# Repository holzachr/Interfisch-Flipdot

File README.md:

This is a fork of "Interfisch"'s brilliant work for creating an ESP32 based "Annax" flipdot module controller board, software and more.

The goals of this fork are
- Re-layouting the controller board to fit the original ADtranz controller board
- Modifying the ESP32 software to support the original ADtranz flipdot module configuration (2x 25x16, 2x 20x16, 1x 25x16)
- Added another useful test pattern (checkers)
- Made flipdot timing parameters settable through MQTT, to help determine ideal settings

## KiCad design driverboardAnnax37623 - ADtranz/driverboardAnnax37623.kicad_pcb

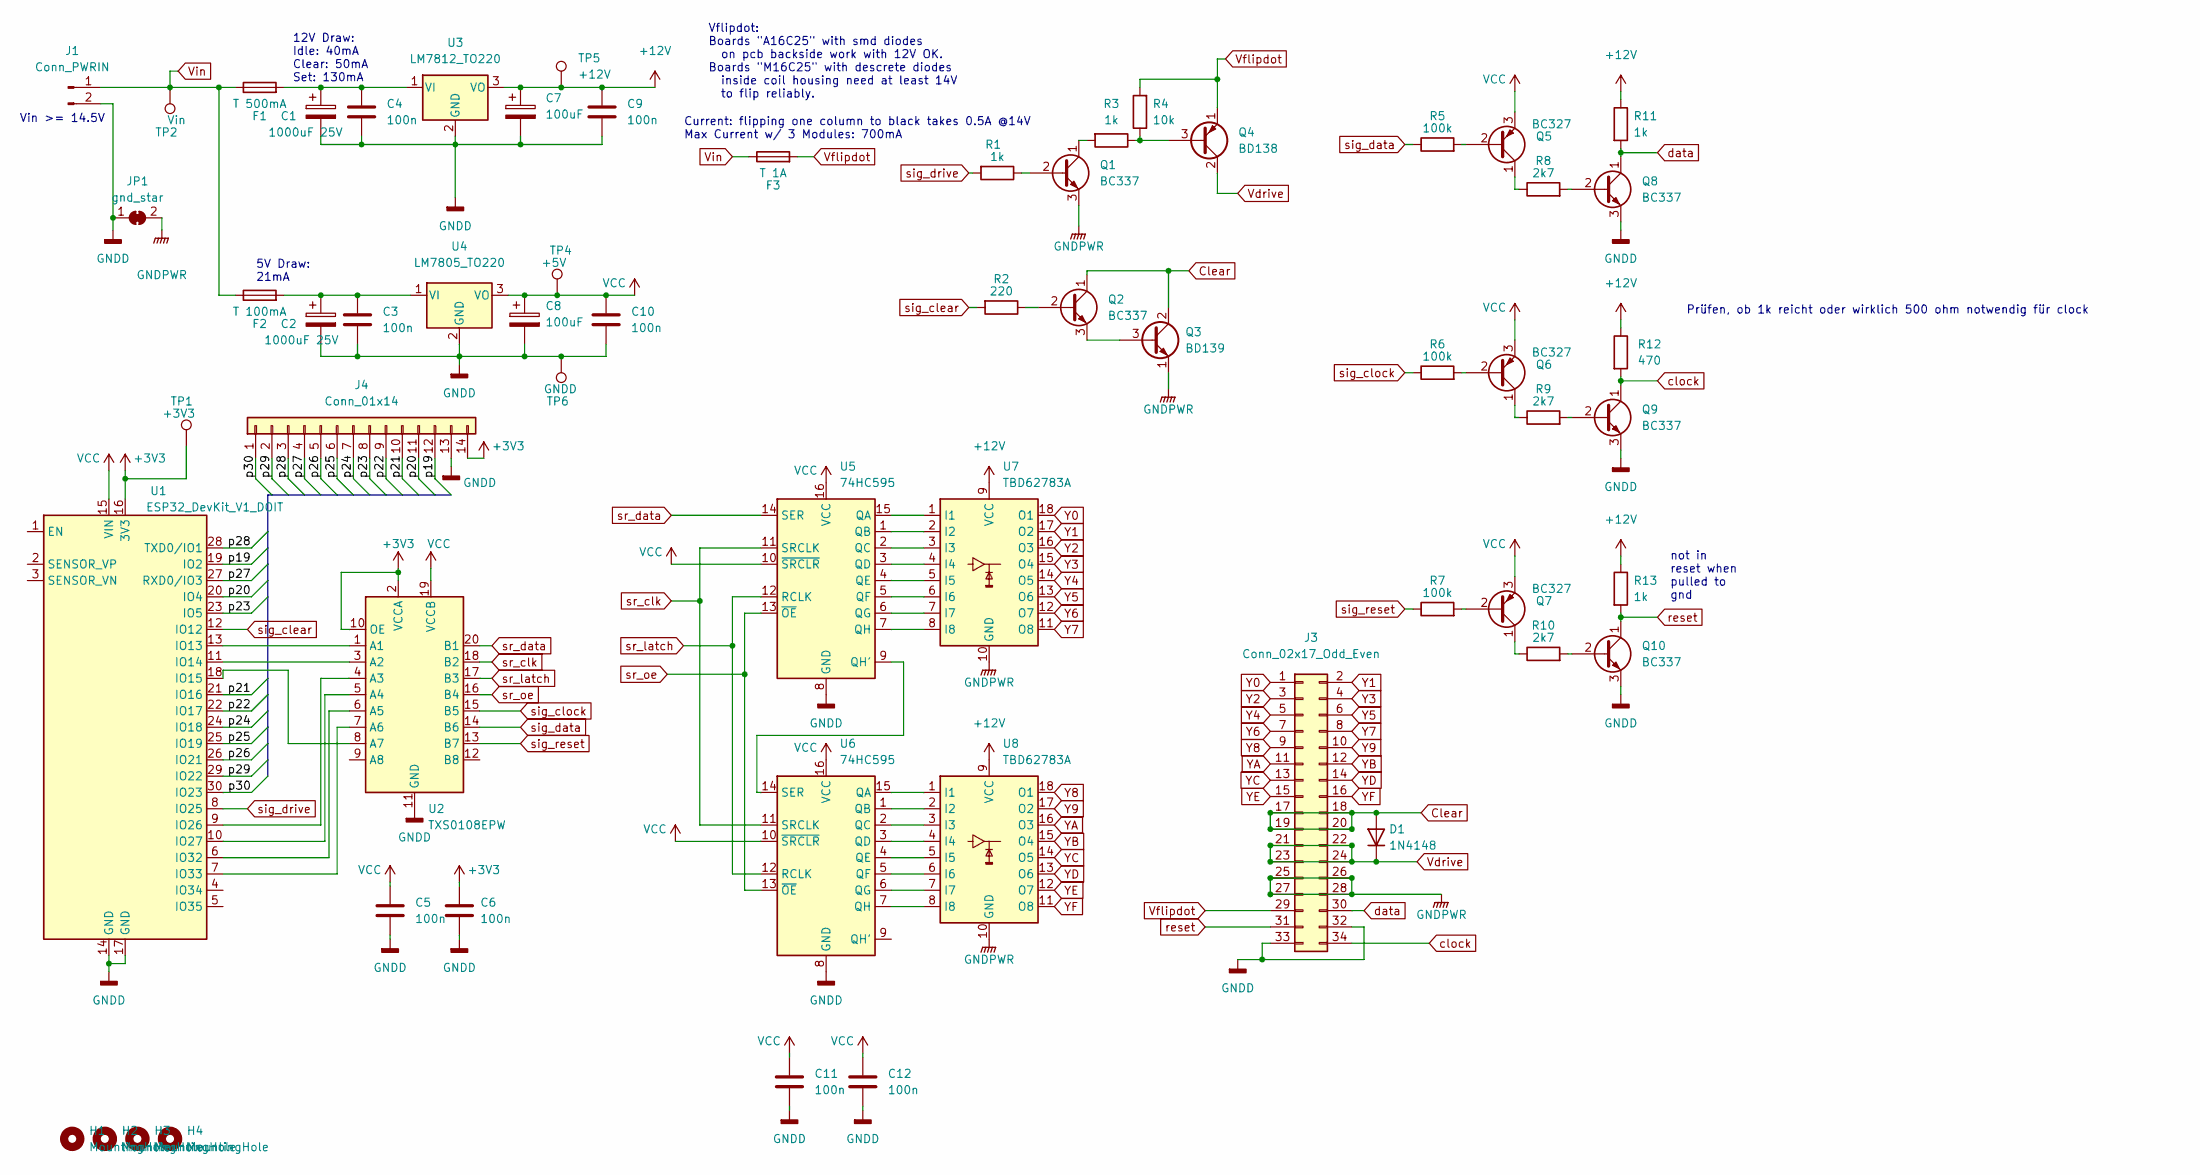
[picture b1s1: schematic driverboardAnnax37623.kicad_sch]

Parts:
C1, C2: 1000uF 25V; CP_Radial_D10.0mm_P5.00mm
C3, C4, C5, C6, C9, C10, C11, C12: 100n; C_Disc_D3.0mm_W2.0mm_P2.50mm
C7, C8: 100uF; CP_Radial_D10.0mm_P5.00mm
D1: 1N4148; D_DO-35_SOD27_P7.62mm_Horizontal
F1: T 500mA; Fuseholder_Clip-5x20mm_Littelfuse_100_Inline_P20.50x4.60mm_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
F2: T 100mA; Fuseholder_Clip-5x20mm_Littelfuse_100_Inline_P20.50x4.60mm_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
F3: T 1A; Fuseholder_Clip-5x20mm_Littelfuse_100_Inline_P20.50x4.60mm_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
H1, H3: MountingHole; MountingHole_4mm
H2, H4: MountingHole; MountingHole_5mm
J1: Conn_PWRIN; TerminalBlock_bornier-2_P5.08mm
J3: Conn_02x17_Odd_Even; IDC-Header_2x17_P2.54mm_Vertical
J4: Conn_01x14; PinHeader_1x14_P2.54mm_Vertical
JP1: gnd_star; PinHeader_1x02_P2.54mm_Vertical
Q1, Q2, Q8, Q9, Q10: BC337; TO-92_Inline
Q3: BD139; TO-126-3_Vertical
Q4: BD138; TO-126-3_Vertical
Q5, Q6, Q7: BC327; TO-92_Inline
R1, R3, R11, R13: 1k; R_Axial_DIN0207_L6.3mm_D2.5mm_P10.16mm_Horizontal
R2: 220; R_Axial_DIN0207_L6.3mm_D2.5mm_P10.16mm_Horizontal
R4: 10k; R_Axial_DIN0207_L6.3mm_D2.5mm_P10.16mm_Horizontal
R5, R6, R7: 100k; R_Axial_DIN0207_L6.3mm_D2.5mm_P10.16mm_Horizontal
R8, R9, R10: 2k7; R_Axial_DIN0207_L6.3mm_D2.5mm_P10.16mm_Horizontal
R12: 470; R_Axial_DIN0207_L6.3mm_D2.5mm_P10.16mm_Horizontal
TP1: +3V3; TestPoint_Bridge_Pitch2.54mm_Drill1.0mm
TP2: Vin; TestPoint_Bridge_Pitch2.54mm_Drill1.0mm
TP4: +5V; TestPoint_Bridge_Pitch2.54mm_Drill1.0mm
TP5: +12V; TestPoint_Bridge_Pitch2.54mm_Drill1.0mm
TP6: GNDD; TestPoint_Bridge_Pitch2.54mm_Drill1.0mm
U1: ESP32_DevKit_V1_DOIT; esp32_devkit_v1_doit
U2: TXS0108EPW; TSSOP-20_4.4x6.5mm_P0.65mm
U3: LM7812_TO220; TO-220-3_Vertical
U4: LM7805_TO220; TO-220-3_Vertical
U5, U6: 74HC595; DIP-16_W7.62mm_Socket_LongPads
U7, U8: TBD62783A; DIP-18_W7.62mm_LongPads

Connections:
+3V3: C6.1, J4.14, TP1.1, U1.16 (3V3), U2.2 (VCCA), U2.10 (OE)
+12V: C7.1, C9.1, R11.1, R12.1, R13.1, TP5.1, U3.3 (VO), U7.9 (VCC), U8.9 (VCC)
/p19: J4.12, U1.19 (IO2)
/p20: J4.11, U1.20 (IO4)
/p21: J4.10, U1.21 (IO16)
/p22: J4.9, U1.22 (IO17)
/p23: J4.8, U1.23 (IO5)
/p24: J4.7, U1.24 (IO18)
/p25: J4.6, U1.25 (IO19)
/p26: J4.5, U1.26 (IO21)
/p27: J4.4, U1.27 (RXD0/IO3)
/p28: J4.3, U1.28 (TXD0/IO1)
/p29: J4.2, U1.29 (IO22)
/p30: J4.1, U1.30 (IO23)
Clear: D1.2 (A), J3.17, J3.18, J3.19, J3.20, Q2.1 (C), Q3.2 (C)
GNDD: C1.2, C2.2, C3.2, C4.2, C5.2, C6.2, C7.2, C8.2, C9.2, C10.2, C11.2, C12.2, J1.2, J3.32, J3.33, J4.13, JP1.1 (A), Q8.3 (E), Q9.3 (E), Q10.3 (E), TP6.1, U1.14 (GND), U1.17 (GND), U2.11 (GND), U3.2 (GND), U4.2 (GND), U5.8 (GND), U6.8 (GND)
GNDPWR: J3.25, J3.26, J3.27, J3.28, JP1.2 (B), Q1.3 (E), Q3.1 (E), U7.10 (GND), U8.10 (GND)
unnamed: Q1.2 (B), R1.1
unnamed: Q1.1 (C), R3.2
unnamed: Q2.2 (B), R2.1
unnamed: Q2.3 (E), Q3.3 (B)
unnamed: Q4.3 (B), R3.1, R4.1
unnamed: Q5.2 (B), R5.2
unnamed: Q5.1 (C), R8.1
unnamed: Q6.2 (B), R6.2
unnamed: Q6.1 (C), R9.1
unnamed: Q7.2 (B), R7.2
unnamed: Q7.1 (C), R10.1
unnamed: Q8.2 (B), R8.2
unnamed: Q9.2 (B), R9.2
unnamed: Q10.2 (B), R10.2
unnamed: U1.13 (IO13), U2.1 (A1)
unnamed: U1.11 (IO14), U2.3 (A2)
unnamed: U1.18 (IO15), U2.8 (A7)
unnamed: U1.9 (IO26), U2.4 (A3)
unnamed: U1.10 (IO27), U2.5 (A4)
unnamed: U1.6 (IO32), U2.6 (A5)
unnamed: U1.7 (IO33), U2.7 (A6)
unnamed: C1.1, C4.1, F1.2, U3.1 (VI)
unnamed: C2.1, C3.1, F2.2, U4.1 (VI)
unnamed: U5.15 (QA), U7.1 (I1)
unnamed: U5.1 (QB), U7.2 (I2)
unnamed: U5.2 (QC), U7.3 (I3)
unnamed: U5.3 (QD), U7.4 (I4)
unnamed: U5.4 (QE), U7.5 (I5)
unnamed: U5.5 (QF), U7.6 (I6)
unnamed: U5.6 (QG), U7.7 (I7)
unnamed: U5.9 (QH'), U6.14 (SER)
unnamed: U5.7 (QH), U7.8 (I8)
unnamed: U6.15 (QA), U8.1 (I1)
unnamed: U6.1 (QB), U8.2 (I2)
unnamed: U6.2 (QC), U8.3 (I3)
unnamed: U6.3 (QD), U8.4 (I4)
unnamed: U6.4 (QE), U8.5 (I5)
unnamed: U6.5 (QF), U8.6 (I6)
unnamed: U6.6 (QG), U8.7 (I7)
unnamed: U6.7 (QH), U8.8 (I8)
VCC: C5.1, C8.1, C10.1, C11.1, C12.1, Q5.3 (E), Q6.3 (E), Q7.3 (E), TP4.1, U1.15 (VIN), U2.19 (VCCB), U4.3 (VO), U5.10 (~SRCLR), U5.16 (VCC), U6.10 (~SRCLR), U6.16 (VCC)
Vdrive: D1.1 (K), J3.21, J3.22, J3.23, J3.24, Q4.2 (C)
Vflipdot: F3.2, J3.29, Q4.1 (E), R4.2
Vin: F1.1, F2.1, F3.1, J1.1, TP2.1
Y0: J3.1, U7.18 (O1)
Y1: J3.2, U7.17 (O2)
Y2: J3.3, U7.16 (O3)
Y3: J3.4, U7.15 (O4)
Y4: J3.5, U7.14 (O5)
Y5: J3.6, U7.13 (O6)
Y6: J3.7, U7.12 (O7)
Y7: J3.8, U7.11 (O8)
Y8: J3.9, U8.18 (O1)
Y9: J3.10, U8.17 (O2)
YA: J3.11, U8.16 (O3)
YB: J3.12, U8.15 (O4)
YC: J3.13, U8.14 (O5)
YD: J3.14, U8.13 (O6)
YE: J3.15, U8.12 (O7)
YF: J3.16, U8.11 (O8)
clock: J3.34, Q9.1 (C), R12.2
data: J3.30, Q8.1 (C), R11.2
reset: J3.31, Q10.1 (C), R13.2
sig_clear: R2.2, U1.12 (IO12)
sig_clock: R6.1, U2.15 (B5)
sig_data: R5.1, U2.14 (B6)
sig_drive: R1.2, U1.8 (IO25)
sig_reset: R7.1, U2.13 (B7)
sr_clk: U2.18 (B2), U5.11 (SRCLK), U6.11 (SRCLK)
sr_data: U2.20 (B1), U5.14 (SER)
sr_latch: U2.17 (B3), U5.12 (RCLK), U6.12 (RCLK)
sr_oe: U2.16 (B4), U5.13 (~OE), U6.13 (~OE)

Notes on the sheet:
Vin >= 14.5V
5V Draw: 21mA
not in reset when pulled to gnd
Current: flipping one column to black takes 0.5A @14V Max Current w/ 3 Modules: 700mA
Prüfen, ob 1k reicht oder wirklich 500 ohm notwendig für clock
Vflipdot: Boards "A16C25" with smd diodes on pcb backside work with 12V OK. Boards "M16C25" with descrete diodes inside coil housing need at least 14V to flip reliably.
12V Draw: Idle: 40mA Clear: 50mA Set: 130mA

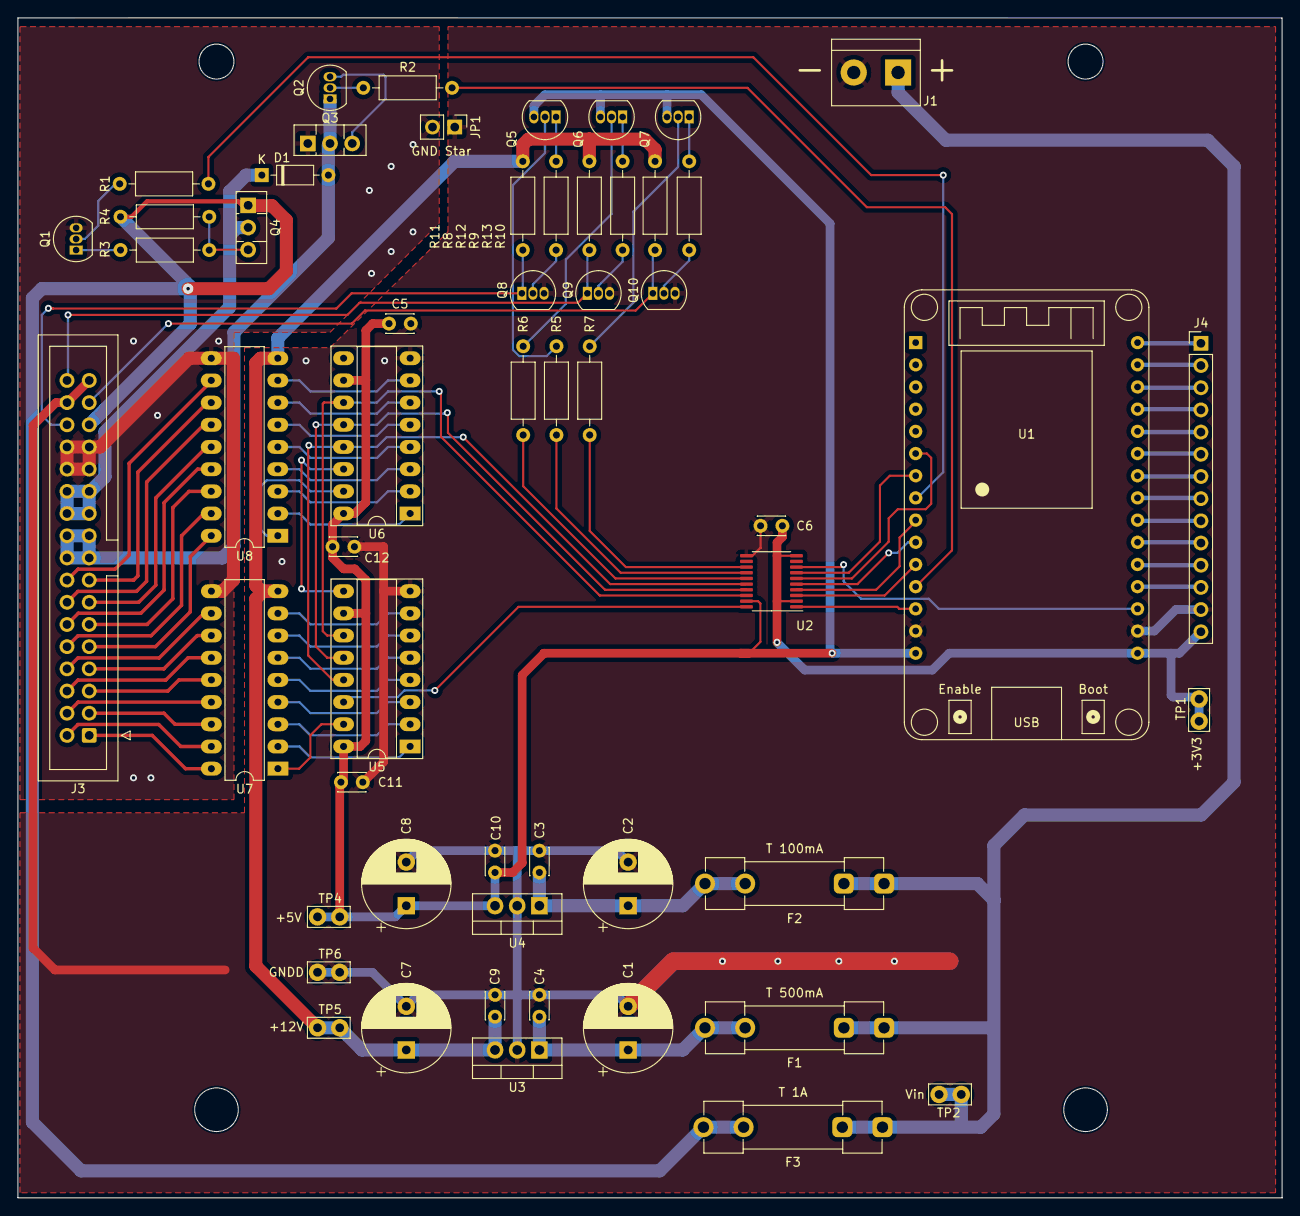
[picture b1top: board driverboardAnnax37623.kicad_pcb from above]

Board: 2 copper layers, 144.7 x 135.1 mm, 60 parts (0 on the bottom side), 89 nets.

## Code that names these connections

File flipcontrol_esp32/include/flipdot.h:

#ifndef FLIPDOT_H
#define FLIPDOT_H

#include <Arduino.h>

#define CHECK_BIT(var,pos) ((var) & (1<<(pos)))

/*
D7 - Ser (data)
D5 - clock
D1 - _OE
D2 - latch
D3 - _clear
*/

//Pins connected to Shift registers on own controller board
#define PIN_SR_DATA 13
#define PIN_SR_CLK 14
#define PIN_SR_OE 27 //active low
#define PIN_SR_LATCH 26

//Pins connected to stuff on annax driver board
#define PIN_DATA_DRVBRD 33
#define PIN_CLK_DRVBRD 32
#define PIN_RESET_DRVBRD 15
#define PIN_DRIVE 25 //enables 12v to panels via transistor
#define PIN_CLEAR 12 //connects CLEAR Pin from Annax board to GND (clears column)

#define COLUMNBYTES 29  //4 columns per byte. one panel has 25 columns.  (int)((numpanels*25)/4+1)


//### Timings ###
// Thight: //TODO optimize
#define MICROS_DRIVEDOTSET   5000 //time dot will be powered for flipping to bright side. in microseconds. 700 sometimes flips too late
#define MICROS_DRIVEDOTCLEAR 3300 //time dot will be powered for flipping to black. in microseconds. always flips at least a whole column. 10000 is too short. last value was 20000

#define MICROS_SHIFTDELAY  19 //shift register clock (100/2 = 1/(100/1000000) Hz). At 16 nothing is flipping!
#define MICROS_SHIFT_LATCH 50 //latch high time for 595 (row drivers)

/*
// These values worked before okay:
#define MICROS_DRIVEDOTSET 1500 //time dot will be powered for flipping to bright side. in microseconds. 700 sometimes flips too late
#define MICROS_DRIVEDOTCLEAR 30000 //time dot will be powered for flipping to black. in microseconds. always flips at least a whole column. 10000 is too short. last value was 20000

#define MICROS_SHIFTDELAY 50/2 //shift register clock (100/2 = 1/(100/1000000) Hz) .at 25/2 nothing is flipping!
#define MICROS_SHIFT_LATCH 100 //latch high time for 595 (row drivers)
*/

/*
//Slower values
#define MICROS_DRIVEDOTSET 5000 //time dot will be powered for flipping to bright side. in microseconds. 700 sometimes flips too late
#define MICROS_DRIVEDOTCLEAR 30000 //time dot will be powered for flipping to black. in microseconds. always flips at least a whole column. 10000 is too short. last value was 20000

#define MICROS_SHIFTDELAY 100/2 //shift register clock (100/2 = 1/(100/1000000) Hz) .at 25/2 nothing is flipping!
#define MICROS_SHIFT_LATCH 200 //latch high time for 595 (row drivers)
*/

class Flipdot
{
    
private:
    bool HBridgeOK();
    void resetColumns();
    void shiftOutSlow(uint8_t dataPin, uint8_t clockPin, uint8_t bitOrder, uint8_t val);

    uint16_t row; //controls shift registers on own controller pcb

    uint8_t col[COLUMNBYTES]; //column drivers and shift registers on annax pcb

    bool rowdata_msbfirst;
    bool column_reversed;

    uint16_t driveDotSetDelayUs;
    uint16_t driveDotClearDelayUs;
    uint16_t shiftDelayUs;
    uint16_t shiftLatchTimeUs;

public:
    Flipdot();
    void init();

    bool clearSelectedColumn();
    bool setSelectedDot();

    void selectColumnClear(uint8_t selcolumn);
    void selectColumnSet(uint8_t selcolumn);
    void selectColumn(uint8_t selcolumn, bool clear);

    void setRow(uint16_t _row);
    uint16_t getRow();

    void shiftDataRow();
    void shiftDataColumn();

    void setDisplayMirror(bool x, bool y);

    void setDriveDotSetDelayUs(uint16_t delayUs);
    void setDriveDotClearDelayUs(uint16_t delayUs);
    void setShiftDelayUs(uint16_t delayUs);
    void setShiftLatchTimeUs(uint16_t timeUs);
};

#endif

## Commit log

2026-04-03 Removed KiCAD backups / old production files
2026-04-07 Added more test presets/patterns.
